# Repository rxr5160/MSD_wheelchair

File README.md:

# MSD_wheelchair
MSD-21311 project, Mind-controlled Wheelchair

wheelchair -> main</br>
left_right -> object detection</br>
steering -> steering and acceleration control</br>
path_planning/ -> contains pathing files and map graph, runs Dijkstra shortest path</br>
	turn
	dijstra
	distance and direction maps
connection/ -> contains communcation code</br>
build.sh -> compiles system, bypass a makefile to run the command in shell</br>

<h3> code structure of Wheelchair main </h3>

- set global variables
	- next node idx
	- turning nodes -> prev, current, next IDs
	- total distnace traveled
	- distnace togo to next node
	- reset flag, boolean
- set start and end nodes from cmd arguments
- setup cameras
- get path through nodes
- set next node and distance to node 
- *loop*
	- get dstance traveled from camera
	- check if at the node -> z distance vs. togo distance
		- adjust total distance traveled
		- set next node and distance togo
		- set reset
	- if reset
		- reset camera pose
		- tell direction to turn
		- move turning node IDs forward
		- clear reset
	- check depth camera
		- adjust turn and acceleration signals as needed
	- send message to chair control of forward and turn intensity
- *end loop*

NOTES
=====
Tracking camera MUST have a USB3.0 controller or it throws an error

Several macros are used in debug for object detection
- ABS, prints average distance for each quadrent
- DET, prints quadrents with marks for threshold detection in each
- PDBG, prints signal it would want to send, turn left/turn right

Steering uses a quick and dirty PID of 10 elements to smooth steering, adjust size as needed (PID_SIZE in steering.cpp)

Object detection distance can be adjusted via the THRESH macro in wheelchair.h

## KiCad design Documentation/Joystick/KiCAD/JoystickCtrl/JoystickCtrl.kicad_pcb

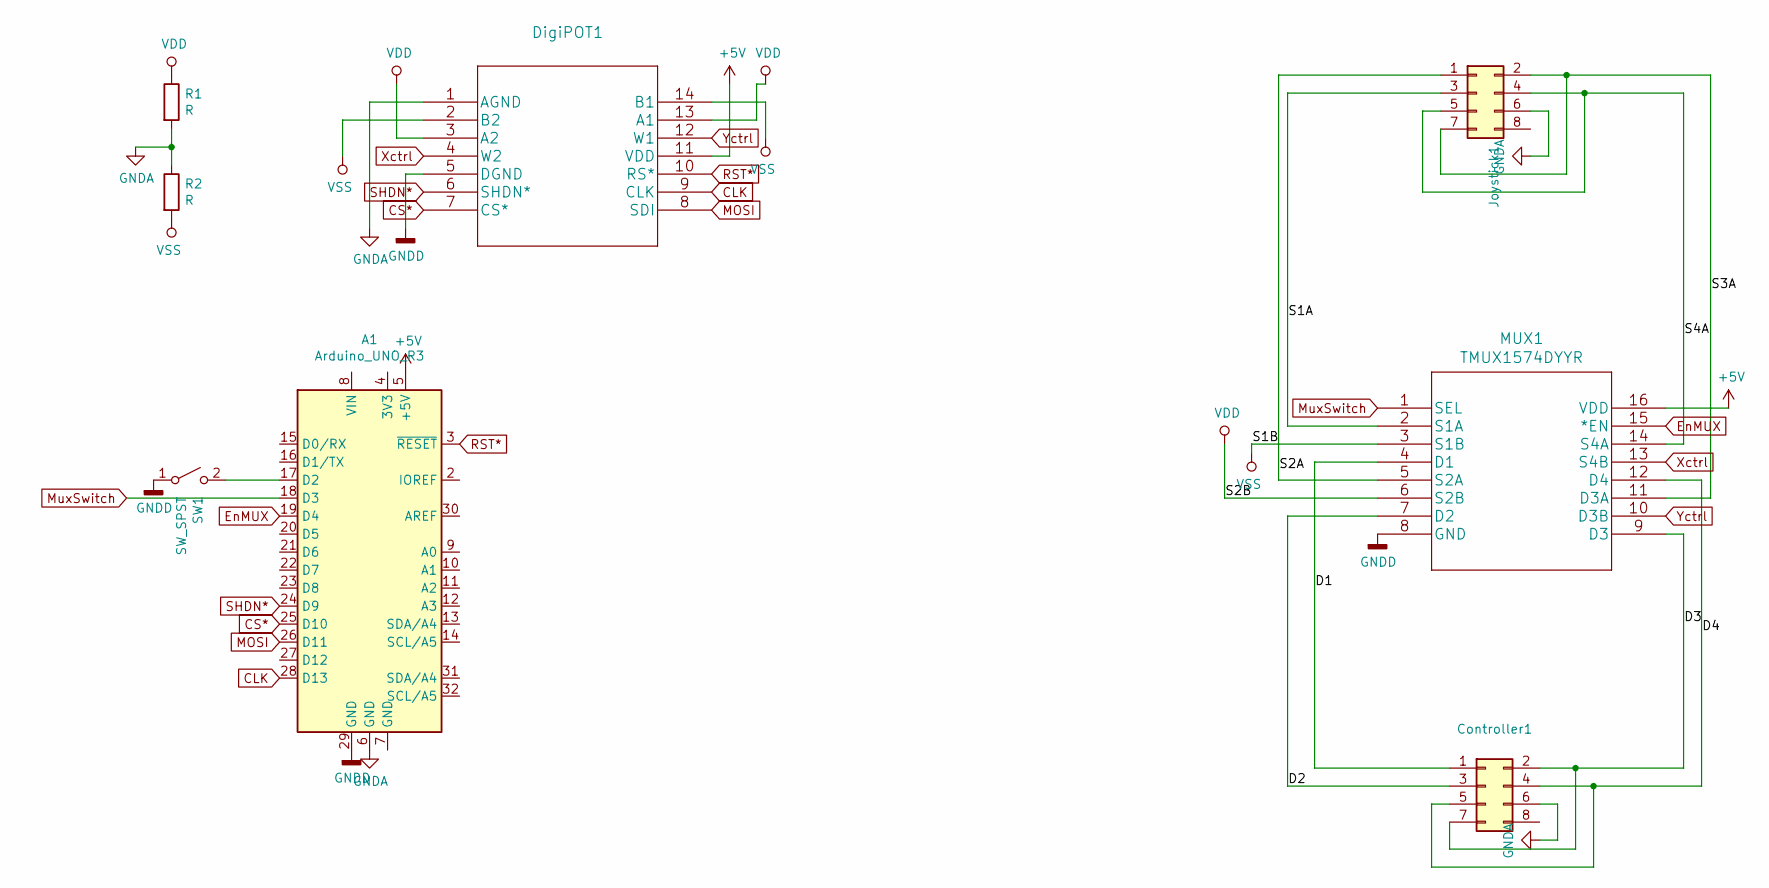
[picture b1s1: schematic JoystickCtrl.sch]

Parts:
A1: Arduino_UNO_R3; Arduino_UNO_R3_WithMountingHoles
Controller1: Conn_02x04_Odd_Even; PinHeader_2x04_P2.00mm_Vertical
DigiPOT1: AD8402ARZ1-REEL; SOIC-14_3.9x8.7mm_P1.27mm
Joystick1: Conn_02x04_Odd_Even; PinHeader_2x04_P2.00mm_Vertical
MUX1: TMUX1574DYYR
R1, R2: R; R_Axial_DIN0207_L6.3mm_D2.5mm_P10.16mm_Horizontal
SW1: SW_SPST; SW_DIP_SPSTx01_Slide_9.78x4.72mm_W7.62mm_P2.54mm

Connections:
+5V: A1.5 (+5V), DigiPOT1.11 (VDD), MUX1.16 (VDD)
/D1: Controller1.1, MUX1.4 (D1)
/D2: Controller1.3, MUX1.7 (D2)
/D3: Controller1.2, Controller1.7, MUX1.9 (D3)
/D4: Controller1.4, Controller1.5, MUX1.12 (D4)
/S1A: Joystick1.3, MUX1.2 (S1A)
/S2A: Joystick1.1, MUX1.5 (S2A)
/S3A: Joystick1.2, Joystick1.7, MUX1.11 (D3A)
/S4A: Joystick1.4, Joystick1.5, MUX1.14 (S4A)
CLK: A1.28 (D13), DigiPOT1.9 (CLK)
CS*: A1.25 (D10), DigiPOT1.7 (CS*)
EnMUX: A1.19 (D4), MUX1.15 (*EN)
GNDA: A1.6 (GND), Controller1.6, DigiPOT1.1 (AGND), Joystick1.6, R1.2, R2.1
GNDD: A1.29 (GND), DigiPOT1.5 (DGND), MUX1.8 (GND), SW1.1 (A)
MOSI: A1.26 (D11), DigiPOT1.8 (SDI)
MuxSwitch: A1.18 (D3), MUX1.1 (SEL)
unnamed: A1.17 (D2), SW1.2 (B)
RST*: A1.3 (~RESET), DigiPOT1.10 (RS*)
SHDN*: A1.24 (D9), DigiPOT1.6 (SHDN*)
VDD: DigiPOT1.3 (A2), DigiPOT1.13 (A1), MUX1.6 (S2B), R1.1
VSS: DigiPOT1.2 (B2), DigiPOT1.14 (B1), MUX1.3 (S1B), R2.2
Xctrl: DigiPOT1.4 (W2), MUX1.13 (S4B)
Yctrl: DigiPOT1.12 (W1), MUX1.10 (D3B)

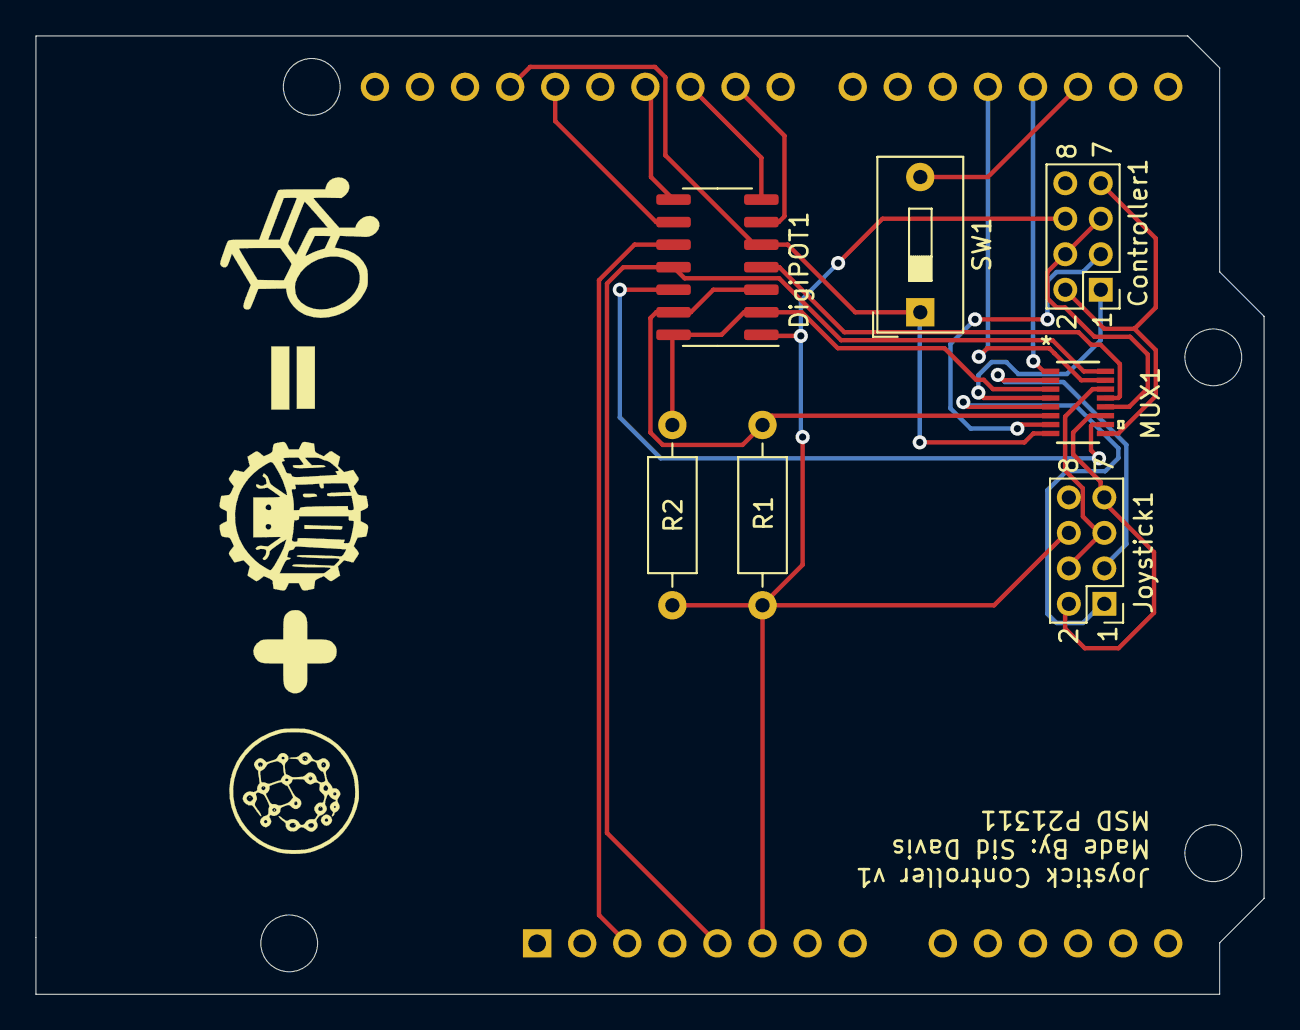
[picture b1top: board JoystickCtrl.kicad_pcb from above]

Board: 2 copper layers, 69.2 x 54.0 mm, 8 parts (1 on the bottom side), 23 nets.

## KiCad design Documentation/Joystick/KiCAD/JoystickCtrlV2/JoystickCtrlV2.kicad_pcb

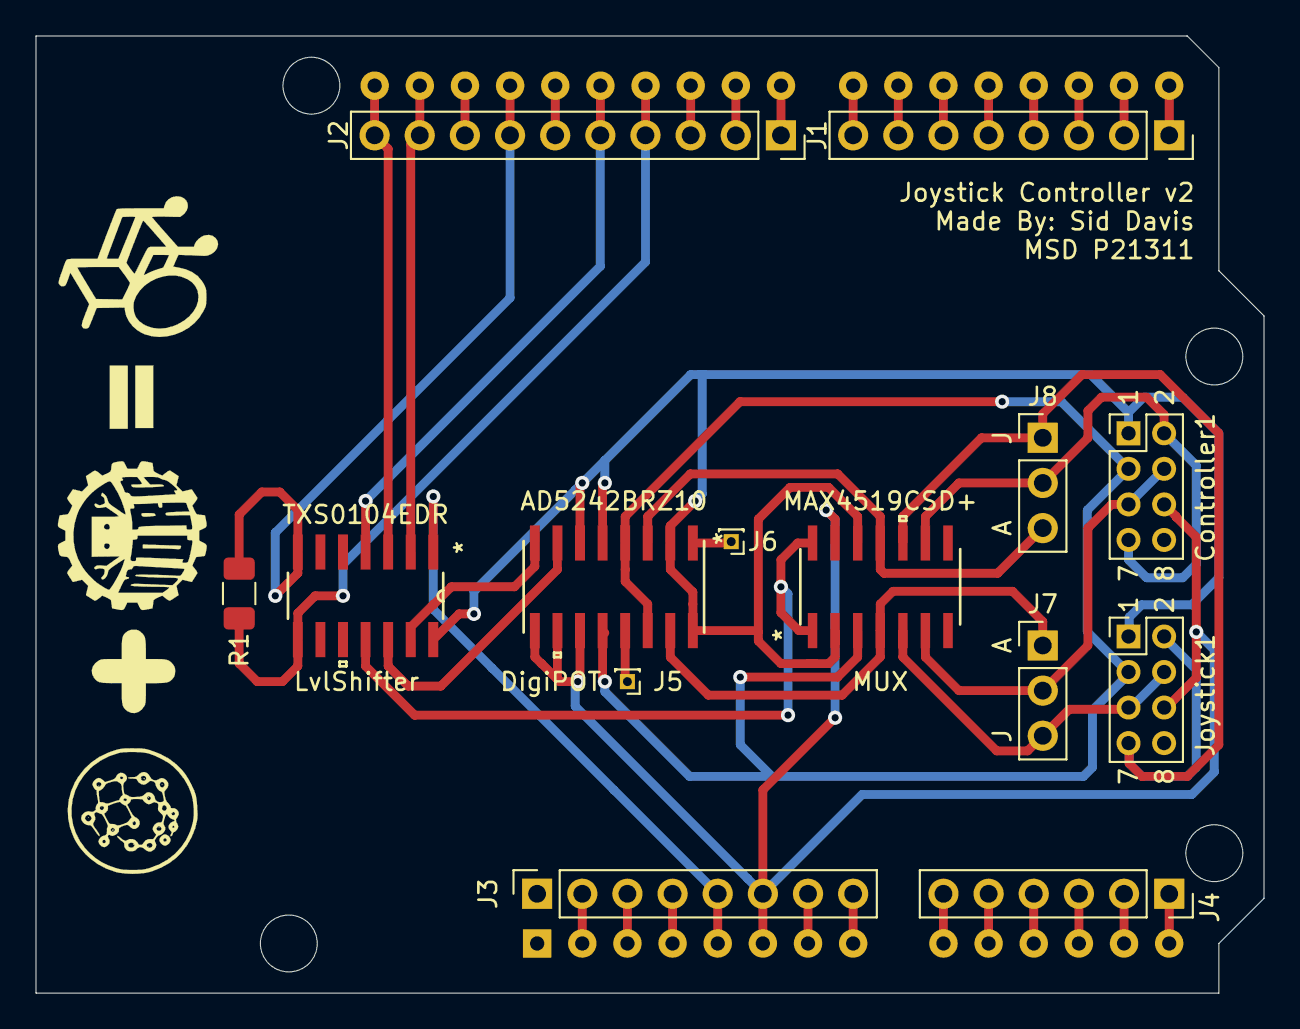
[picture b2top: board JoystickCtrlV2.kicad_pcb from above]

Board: 2 copper layers, 69.1 x 53.8 mm, 15 parts (1 on the bottom side), 42 nets.

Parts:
A1: Arduino_UNO_R3; Arduino_UNO_R3_WithMountingHoles
Controller1: Conn_02x04_Odd_Even; PinHeader_2x04_P2.00mm_Vertical
DigiPOT: AD5242BRZ10
J1, J3: Conn_01x08_Male; PinSocket_1x08_P2.54mm_Vertical
J2: Conn_01x10_Male; PinSocket_1x10_P2.54mm_Vertical
J4: Conn_01x06_Male; PinSocket_1x06_P2.54mm_Vertical
J5: O2; PinHeader_1x01_P1.00mm_Vertical
J6: O1; PinHeader_1x01_P1.00mm_Vertical
J7: Y; PinHeader_1x03_P2.54mm_Vertical
J8: X; PinHeader_1x03_P2.54mm_Vertical
Joystick1: Conn_02x04_Odd_Even; PinHeader_2x04_P2.00mm_Vertical
LvlShifter: TXS0104EDR
MUX: MAX4519CSD+; MAX4519CSD&plus_
R1: 10k; R_1206_3216Metric

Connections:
+2V5: Controller1.1, DigiPOT.2, DigiPOT.5, DigiPOT.6, DigiPOT.16, Joystick1.1, LvlShifter.14, MUX.2, MUX.12
+5V: A1.5, J3.5, LvlShifter.1
-2V5: Controller1.3, DigiPOT.4, DigiPOT.12, DigiPOT.14, Joystick1.3, MUX.3
Ard_MUX: A1.27, J2.5, LvlShifter.4
Ard_SCL: A1.32, J2.10, LvlShifter.3
Ard_SDA: A1.31, J2.9, LvlShifter.2
Ctrl_MUX: LvlShifter.11, MUX.1, MUX.14
Ctrl_X: Controller1.2, Controller1.7, J8.2, MUX.9
Ctrl_Y: Controller1.4, Controller1.5, J7.2, MUX.6
Digi_SCL: DigiPOT.7, LvlShifter.12
Digi_SDA: DigiPOT.8, LvlShifter.13
Digi_X: DigiPOT.3, J8.3, MUX.11
Digi_Y: DigiPOT.15, J7.1, MUX.4
GNDREF: A1.6, A1.7, A1.29, Controller1.6, DigiPOT.9, DigiPOT.10, DigiPOT.11, J2.7, J3.6, J3.7, Joystick1.6, LvlShifter.7, MUX.13, R1.2
Joy_X: J8.1, Joystick1.2, Joystick1.7, MUX.10
Joy_Y: J7.3, Joystick1.4, Joystick1.5, MUX.5
unnamed: A1.2, J3.2
unnamed: A1.3, J3.3
unnamed: A1.4, J3.4
unnamed: A1.8, J3.8
unnamed: A1.9, J4.6
unnamed: A1.10, J4.5
unnamed: A1.11, J4.4
unnamed: A1.12, J4.3
unnamed: A1.13, J4.2
unnamed: A1.14, J4.1
unnamed: A1.15, J1.1
unnamed: A1.16, J1.2
unnamed: A1.17, J1.3
unnamed: A1.18, J1.4
unnamed: A1.19, J1.5
unnamed: A1.20, J1.6
unnamed: A1.21, J1.7
unnamed: A1.22, J1.8
unnamed: A1.23, J2.1
unnamed: A1.24, J2.2
unnamed: A1.25, J2.3
unnamed: A1.28, J2.6
unnamed: A1.30, J2.8
unnamed: DigiPOT.1, J6.1
unnamed: DigiPOT.13, J5.1
Shft_En: A1.26, J2.4, LvlShifter.8, R1.1

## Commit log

2020-10-08 added intel examples and gitignore
2020-10-08 touched README
2020-10-08 read data from pose imu
2020-10-08 README noted
2020-10-08 wall detection v1
2020-10-13 Added code from Oct 8th to fix connection
2020-10-15 Fixed the incrementing of total_dist
2020-10-15 multicam doc copy
2021-03-01 thirds large object det
2021-03-01 16 quardrents
2021-03-01 coordinate system and blocking - tells if close in Qx, threshhold macro
2021-03-01 macro dor raw distance vs thing det
2021-03-01 todo comments, monday
2021-03-02 added grid and left/right message
2021-03-07 started graph stubs
2021-03-08 added turn left/right print in side to side detection section
2021-03-08 Adjacency list design changed
2021-03-08 split main into functions
2021-03-08 Added dual cameras to left_right as main function
2021-03-08 Attempt to reset pose
2021-03-08 first pass at traversal - need debug
2021-03-08 syntax changes
2021-03-08 more debug of inital traversal
2021-03-08 extended example graph
2021-03-08 visted check
2021-03-08 debug - still segfaulting on auto in traversal
2021-03-10 Updated errors from graph. Added location names with index reference
2021-03-15 path finding gets a path, not minimal
2021-03-15 Reset device pose, added new path planning
2021-03-17 Updating the layout of files for better integration
2021-03-17 grap/map file and location to node correlation
2021-03-17 changed pathfinding to use our map
2021-03-17 Added bash for easy compiling
2021-03-17 removed a.out
2021-03-17 two-way map
2021-03-17 Fixed reference of mapping from main
2021-03-17 Removed unused return
2021-03-22 distance check
2021-03-22 compilation error fixes
2021-03-22 readme updated with structre
2021-03-22 Update README.md
    updated README structure
2021-03-22 few more print/readme adjustments
2021-03-22 im really struggling with getting the readme how I want
2021-03-22 more changes/cleanup of stich code, needs more
2021-03-22 removed old examples, no longer relavant
2021-03-24 directional control stick working - no comunication yet
2021-03-24 added connection sub dir
2021-03-29 cleaned up wheelchair files, added turn read coment
2021-03-31 compiation fix
2021-03-31 pirnt correction
2021-03-31 Nothing
2021-03-31 Needed a space
2021-04-05 Added serial design - code will not compile at the moment
2021-04-07 steer and accel control v1
2021-04-07 Implemented serial, installed zeromq library
2021-04-12 removed bottom row - commented
2021-04-12 cleaned up pid and maths in steering
2021-04-12 fixed more maths in steering
2021-04-12 Updated arduino to close nicely
2021-04-12 documentation inside files - added signal handler in main
2021-04-12 some more comment adjustemts for documentatioin and readabilty
2021-04-12 Modified signal handler to shutdown properly
2021-04-12 clean for celan exit now with signal handler
2021-04-12 Fixed warnings for missing include and declaration
2021-04-14 steering and pathing debug session
2021-04-14 wall checking back in, panic stop if obj too close
2021-04-14 Created directions list, first line is layout of data inside
2021-04-21 first turn run, memory issues
2021-04-21 Work on headset server for non blocking
    removed wheelchair
2021-04-21 Fixed string split memory issues
2021-04-21 seg fix
2021-04-21 le push
2021-04-21 Remembered that straight is an option for testing
2021-04-21 started main file integration - need node info
2021-04-26 Work in progress of headset server side
2021-04-26 Blocked receive set up. Small adjustments to be made for full integration
2021-04-28 turn checking fir run for directional tells
2021-04-28 Integrated headset connection with main
2021-04-28 safer in turn indexing
2021-04-28 erroring with testing comments
2021-04-28 testing attempts - seg fault
2021-04-28 resolved segfault
2021-04-28 Update README.md
    added turning into high level code flow in readme
2021-04-28 Fixed headset address error
2021-05-11 Config Directory
2021-05-11 Documentation
2021-05-11 Shared Technical Papers
2021-05-11 Original Wheelchair Files
2021-05-11 3D Models from OnShape
2021-05-11 Joystick Docs, Code, & PCBs
2021-05-11 Pictures
2021-05-11 Camera Docs
2021-05-11 MSD Documentation
    HoQ, PRP, BOM, & Risks

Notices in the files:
parts and their libraries:
Copyright 2016 Accelerated Designs. All rights reserved.
